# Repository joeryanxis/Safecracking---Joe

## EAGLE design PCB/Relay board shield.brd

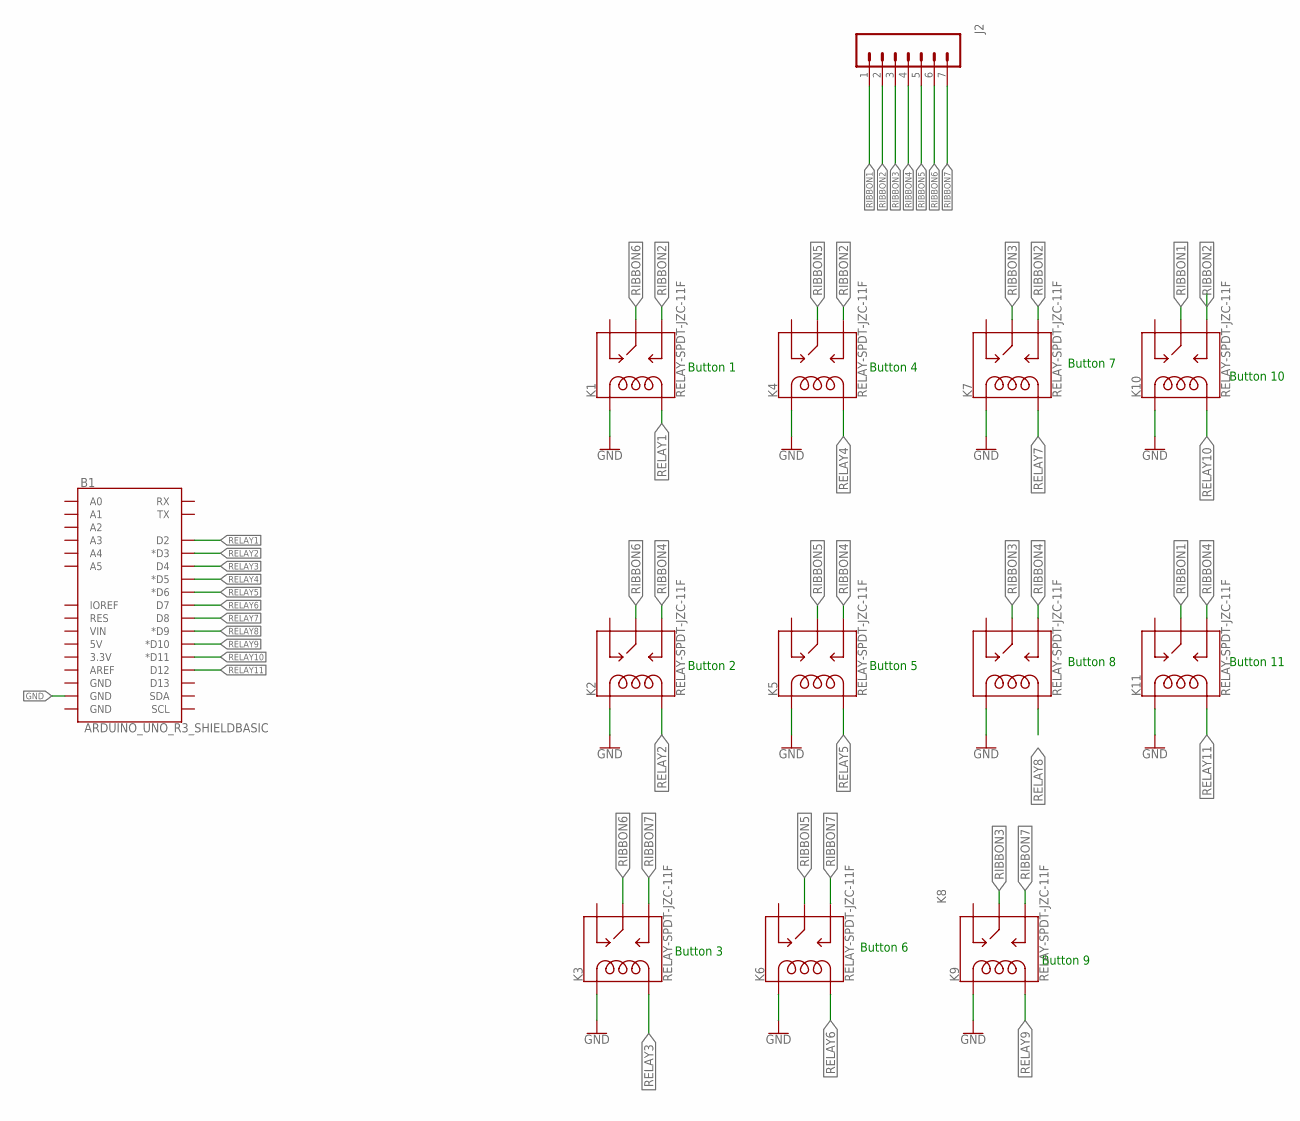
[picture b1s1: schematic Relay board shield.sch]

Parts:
B1: ARDUINO_UNO_R3_SHIELDBASIC; UNO_R3_SHIELD
J2: CONN_07; 1X07
K1, K2, K3, K4, K5, K6, K7, K8, K9, K10, K11: RELAY-SPDT-JZC-11F; RELAY-JZC

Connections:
GND: B1.GND@1 (GND), K1.5 (COIL1), K2.5 (COIL1), K3.5 (COIL1), K4.5 (COIL1), K5.5 (COIL1), K6.5 (COIL1), K7.5 (COIL1), K8.5 (COIL1), K9.5 (COIL1), K10.5 (COIL1), K11.5 (COIL1)
RELAY1: B1.D2, K1.1 (COIL2)
RELAY2: B1.D3 (*D3), K2.1 (COIL2)
RELAY3: B1.D4, K3.1 (COIL2)
RELAY4: B1.D5 (*D5), K4.1 (COIL2)
RELAY5: B1.D6 (*D6), K5.1 (COIL2)
RELAY6: B1.D7, K6.1 (COIL2)
RELAY7: B1.D8, K7.1 (COIL2)
RELAY8: B1.D9 (*D9), K8.1 (COIL2)
RELAY9: B1.D10 (*D10), K9.1 (COIL2)
RELAY10: B1.D11 (*D11), K10.1 (COIL2)
RELAY11: B1.D12, K11.1 (COIL2)
RIBBON1: J2.1, K10.4 (MAIN), K11.4 (MAIN)
RIBBON2: J2.2, K1.3 (NO), K4.3 (NO), K7.3 (NO), K10.3 (NO)
RIBBON3: J2.3, K7.4 (MAIN), K8.4 (MAIN), K9.4 (MAIN)
RIBBON4: J2.4, K2.3 (NO), K5.3 (NO), K8.3 (NO), K11.3 (NO)
RIBBON5: J2.5, K4.4 (MAIN), K5.4 (MAIN), K6.4 (MAIN)
RIBBON6: J2.6, K1.4 (MAIN), K2.4 (MAIN), K3.4 (MAIN)
RIBBON7: J2.7, K3.3 (NO), K6.3 (NO), K9.3 (NO)

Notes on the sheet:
Button 1
Button 2
Button 3
Button 4
Button 5
Button 6
Button 7
Button 8
Button 9
Button 10
Button 11

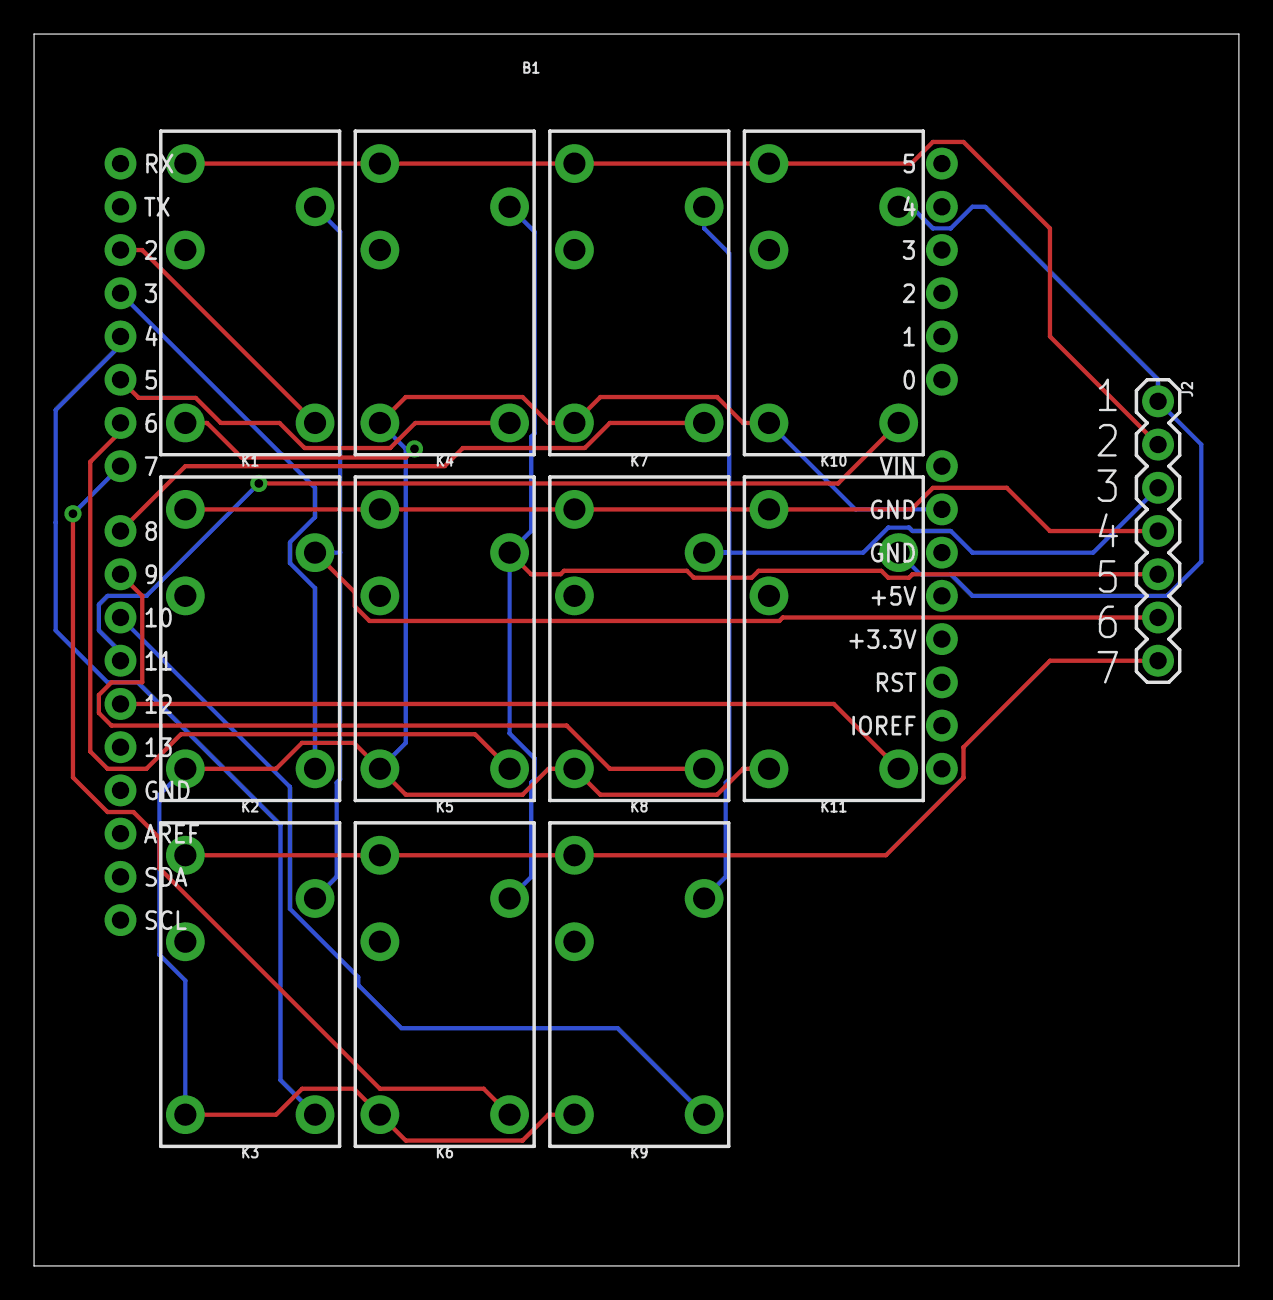
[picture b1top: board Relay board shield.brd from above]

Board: 2 copper layers, 70.8 x 72.4 mm, 13 parts (0 on the bottom side), 19 nets.

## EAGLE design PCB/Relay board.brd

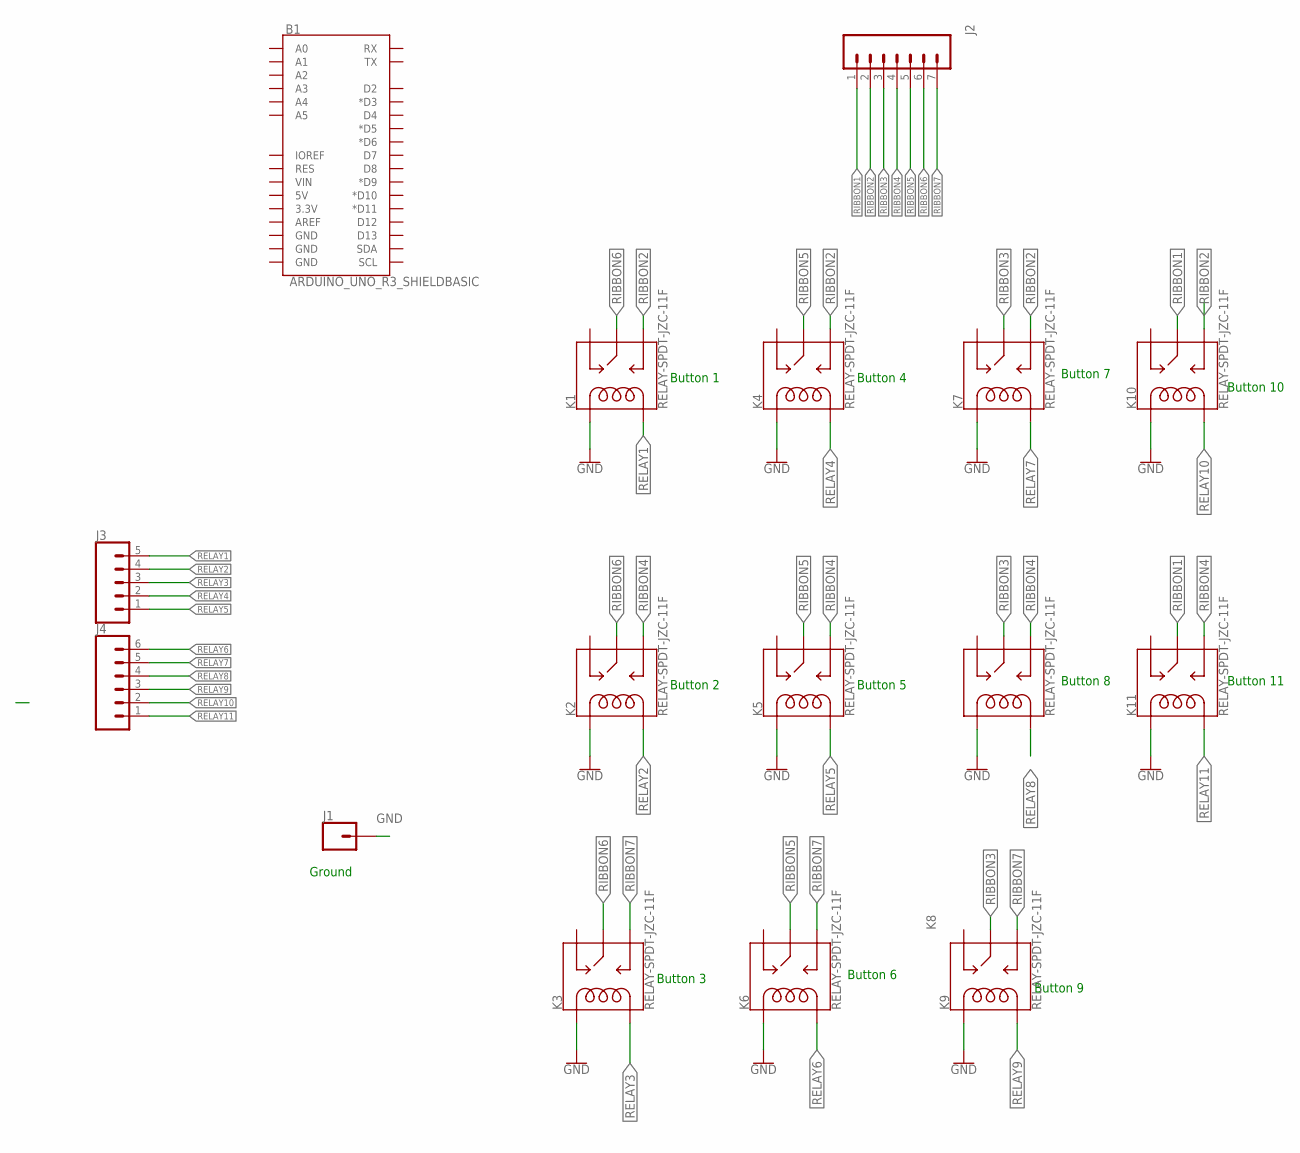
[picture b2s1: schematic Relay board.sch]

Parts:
B1: ARDUINO_UNO_R3_SHIELDBASIC; UNO_R3_SHIELD
J1: CONN_01; 1X01
J2: CONN_07; 1X07
J3: CONN_05; 1X05
J4: CONN_06SILK_FEMALE_PTH; 1X06
K1, K2, K3, K4, K5, K6, K7, K8, K9, K10, K11: RELAY-SPDT-JZC-11F; RELAY-JZC

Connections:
GND: J1.1, K1.5 (COIL1), K2.5 (COIL1), K3.5 (COIL1), K4.5 (COIL1), K5.5 (COIL1), K6.5 (COIL1), K7.5 (COIL1), K8.5 (COIL1), K9.5 (COIL1), K10.5 (COIL1), K11.5 (COIL1)
RELAY1: J3.5, K1.1 (COIL2)
RELAY2: J3.4, K2.1 (COIL2)
RELAY3: J3.3, K3.1 (COIL2)
RELAY4: J3.2, K4.1 (COIL2)
RELAY5: J3.1, K5.1 (COIL2)
RELAY6: J4.6, K6.1 (COIL2)
RELAY7: J4.5, K7.1 (COIL2)
RELAY8: J4.4, K8.1 (COIL2)
RELAY9: J4.3, K9.1 (COIL2)
RELAY10: J4.2, K10.1 (COIL2)
RELAY11: J4.1, K11.1 (COIL2)
RIBBON1: J2.1, K10.4 (MAIN), K11.4 (MAIN)
RIBBON2: J2.2, K1.3 (NO), K4.3 (NO), K7.3 (NO), K10.3 (NO)
RIBBON3: J2.3, K7.4 (MAIN), K8.4 (MAIN), K9.4 (MAIN)
RIBBON4: J2.4, K2.3 (NO), K5.3 (NO), K8.3 (NO), K11.3 (NO)
RIBBON5: J2.5, K4.4 (MAIN), K5.4 (MAIN), K6.4 (MAIN)
RIBBON6: J2.6, K1.4 (MAIN), K2.4 (MAIN), K3.4 (MAIN)
RIBBON7: J2.7, K3.3 (NO), K6.3 (NO), K9.3 (NO)

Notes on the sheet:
Button 1
Button 2
Button 3
Button 4
Button 5
Button 6
Button 7
Button 8
Button 9
Button 10
Button 11
Ground

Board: 2 copper layers, 16 parts (0 on the bottom side), 19 nets, no tracks yet.

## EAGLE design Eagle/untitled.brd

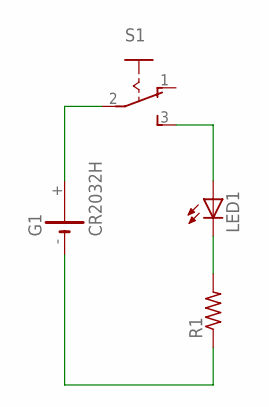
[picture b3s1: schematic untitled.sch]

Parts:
G1: CR2032H
LED1: LED5MM
R1: R-US_0207/10; 0207/10
S1: 255SB

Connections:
unnamed: G1.+, S1.2
unnamed: LED1.A, S1.3 (S)
unnamed: LED1.K (C), R1.2
unnamed: G1.-, R1.1

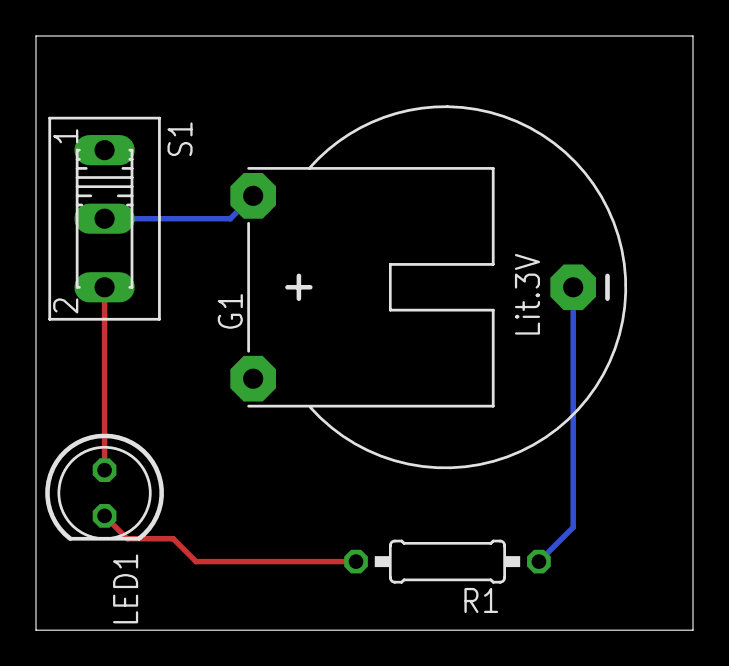
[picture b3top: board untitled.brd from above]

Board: 2 copper layers, 36.5 x 33.0 mm, 4 parts (0 on the bottom side), 4 nets.

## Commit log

2018-10-15 Initial upload
    Uploading all the files I've worked on thie semester so far
2018-10-18 Updated handle puller
    10% wider
2018-10-30 Update
    Includes PCB files, relay arduino code, and algorithm for going through all possible combinations
2018-10-30 finished pcb

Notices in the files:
parts and their libraries:
SparkFun-Electromechanical: Licensing: Creative Commons ShareAlike 4.0 International - https://creativecommons.org/licenses/by-sa/4.0
